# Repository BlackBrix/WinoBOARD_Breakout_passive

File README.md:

## Breakout-Board (passive) for the Wino-Board

This is a breadboard compatible Breakout-Board for the WinoBOARD (http://wino-board.com).  
The WinoBOARD comes with 2.0 mm spaced pin headers, so you can NOT use it with any standard (solder-less) breadboard / prototyping PCB (stripes or holes) out of the box...

### Features:
* pin spacing 0,1 inch / 100 mil / 2,54 mm
* 900 mil (22.86 mm) spacing between the 2 outer rows of pin headers
* therefore it fits on every standard (solder-less) breadboard / prototyping PCB (stripes or holes)
* smallest possible size: 25,4 mm x 35,56mm (1 inch x 1,4 inch)
* "sorted" I/Os (see picture)
* you may solder the WinoBOARD directly onto the this Breakout-Board or use (2mm-pin-spacing) sockets (recommended)
* cut-out in ground-plane for not disturbing the WiFi antenna
* has 2 mounting holes [2,2 mm] for M2-screws (e.g. for later use within another housing / or with your own projects)

This Breakout-Board is completely "passive" (no active components),  
that means, you have to manage the power supply (3.3V) and USB-connection and reset-button by yourself,  
or you use the USB-/Battery upgrade (http://wino-board.com/upgrades/usb-battery-upgrade)  
which is of course usable (stackable) with this Breakout-Board as well.

---

[I am in no way associated with the manufacturer of the original WinoBOARD]

get one -> [https://www.tindie.com/stores/blackbrix/](https://www.tindie.com/stores/blackbrix/)

---

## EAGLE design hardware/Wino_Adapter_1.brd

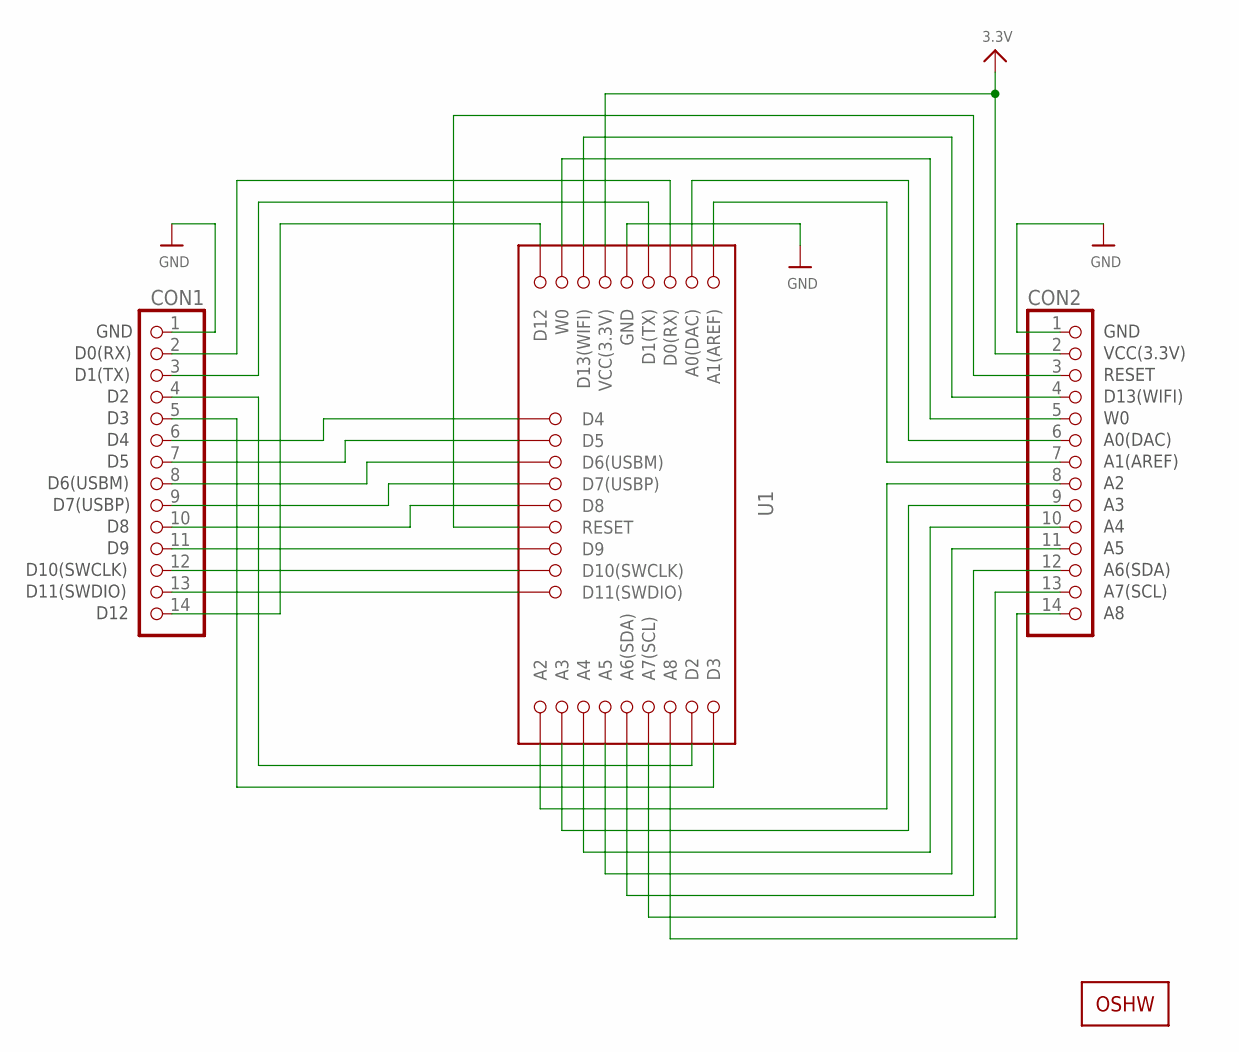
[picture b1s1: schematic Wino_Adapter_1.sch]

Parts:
CON1, CON2: HEADER-1X14; 1X14_ROUND_70
LOGO1: OSHW_LOGOX0150; OSHW_6X150
U1: WINO_BOARD_EINLOET

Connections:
3.3V: CON2.2, U1.VCC (VCC(3.3V))
GND: CON1.1, CON2.1, U1.GND
unnamed: CON1.2, U1.D0 (D0(RX))
unnamed: CON1.3, U1.D1 (D1(TX))
unnamed: CON1.4, U1.D2
unnamed: CON1.5, U1.D3
unnamed: CON1.6, U1.D4
unnamed: CON1.7, U1.D5
unnamed: CON1.8, U1.D6 (D6(USBM))
unnamed: CON1.9, U1.D7 (D7(USBP))
unnamed: CON1.10, U1.D8
unnamed: CON1.13, U1.D11 (D11(SWDIO))
unnamed: CON1.12, U1.D10 (D10(SWCLK))
unnamed: CON1.11, U1.D9
unnamed: CON1.14, U1.D12
unnamed: CON2.4, U1.D13(WIFI)
unnamed: CON2.6, U1.A0 (A0(DAC))
unnamed: CON2.7, U1.A1 (A1(AREF))
unnamed: CON2.8, U1.A2
unnamed: CON2.9, U1.A3
unnamed: CON2.10, U1.A4
unnamed: CON2.11, U1.A5
unnamed: CON2.12, U1.A6 (A6(SDA))
unnamed: CON2.13, U1.A7 (A7(SCL))
unnamed: CON2.14, U1.A8
unnamed: CON2.3, U1.RESET
unnamed: CON2.5, U1.W0

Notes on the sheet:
D0(RX)
D1(TX)
D6(USBM)
D7(USBP)
D10(SWCLK)
D11(SWDIO)
D12
GND
VCC(3.3V)
RESET
D13(WIFI)
A0(DAC)
A1(AREF)
A6(SDA)
A7(SCL)

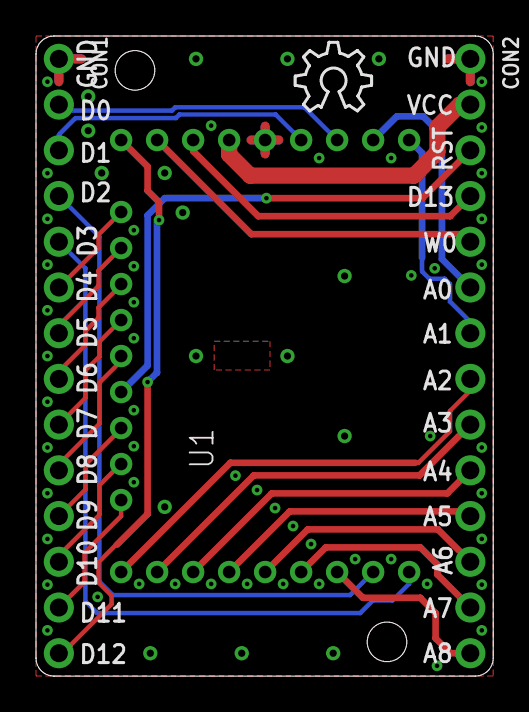
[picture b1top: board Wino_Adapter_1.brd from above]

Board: 2 copper layers, 25.4 x 35.6 mm, 4 parts (0 on the bottom side), 27 nets.

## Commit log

2016-02-25 Added files via upload
2016-02-25 Create test

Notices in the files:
parts and their libraries:
microbuilder: This work is placed in the public domain, and may be freely used for commercial and non-commercial work with the following conditions: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
